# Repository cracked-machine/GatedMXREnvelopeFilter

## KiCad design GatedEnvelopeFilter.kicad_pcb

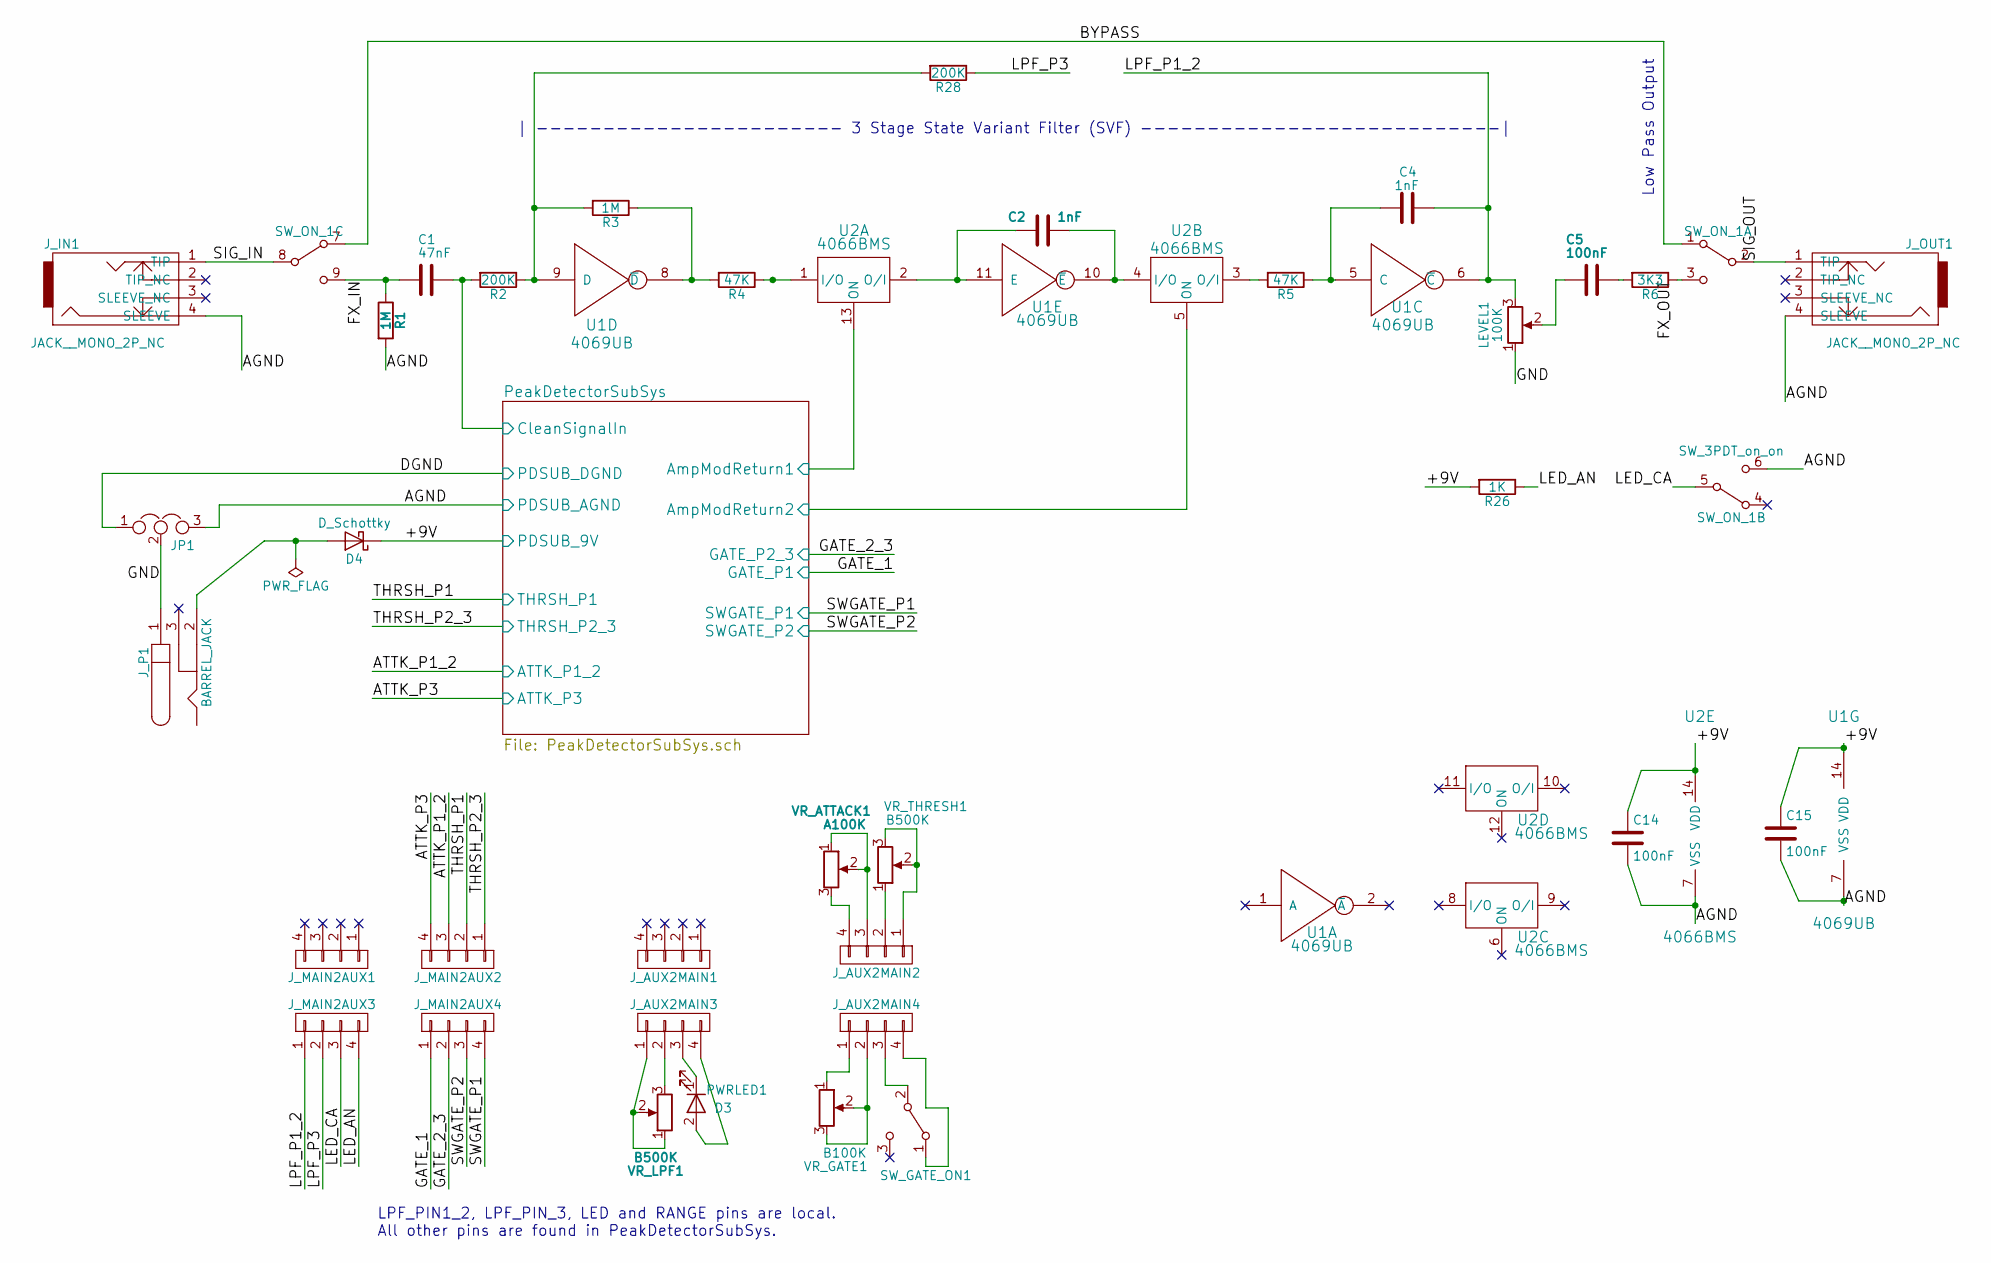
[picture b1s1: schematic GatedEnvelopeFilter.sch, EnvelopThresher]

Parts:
C1: 47nF; C_0805_HandSoldering
C2, C4: 1nF; C_0805_HandSoldering
C5, C14, C15: 100nF; C_0805_HandSoldering
D3: PWRLED1; LED_D5.0mm
D4: D_Schottky; D_SOD-123
JP1: Jumper_NC_Dual; NetTie-II_SMD
J_AUX2MAIN1, J_AUX2MAIN2, J_AUX2MAIN3, J_AUX2MAIN4: CONN_01X04; Pin_Header_Straight_1x04_Pitch2.54mm
J_IN1: JACK__MONO_2P_NC; NeutrikAudioSocket_Mono_PCB_NARROWPADS
J_MAIN2AUX1, J_MAIN2AUX2, J_MAIN2AUX3, J_MAIN2AUX4: CONN_01X04; Pin_Header_Straight_1x04_Pitch2.54mm
J_OUT1: JACK__MONO_2P_NC; NeutrikAudioSocket_Mono_PCB_NARROWPADS
J_P1: BARREL_JACK
LEVEL1: 100K
R1, R3: 1M; R_0805_HandSoldering
R2, R28: 200K; R_0805_HandSoldering
R4, R5: 47K; R_0805_HandSoldering
R6: 3K3; R_0805_HandSoldering
R26: 1K; R_0805_HandSoldering
SW_GATE_ON1: SW_SPDT; SW_SPDT_W6.86MM_L12.7MM_P4.8MM_D2MM
SW_ON_1: SW_3PDT_on_on; SW_3PDT_W18MM_L17.3MM_P5.3MM_D2MM_SolderLugs
U1: 4069UB; SOIC-14_3.9x8.7mm_Pitch1.27mm
U2: 4066BMS; SOIC-14_3.9x8.7mm_Pitch1.27mm
VR_ATTACK1: A100K; Potentiometer_Bourns_PTV09A-1_Horizontal
VR_GATE1: B100K; Potentiometer_Bourns_PTV09A-1_Horizontal
VR_LPF1: B500K; Potentiometer_Bourns_PTV09A-1_Horizontal
VR_THRESH1: B500K; Potentiometer_Bourns_PTV09A-1_Horizontal

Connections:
/+9V: C14.1, C15.1, D4.1 (K), R26.2, U1.14 (VDD), U2.14 (VDD); also elsewhere on the board
/AGND: C14.2, C15.2, JP1.3, J_IN1.4 (SLEEVE), J_OUT1.4 (SLEEVE), R1.2, SW_ON_1.6 (C), U1.7 (VSS), U2.7 (VSS); also elsewhere on the board
/ATTK_P1_2: J_MAIN2AUX2.3; also elsewhere on the board
/ATTK_P3: J_MAIN2AUX2.4; also elsewhere on the board
/BYPASS: SW_ON_1.1 (A), SW_ON_1.7 (A)
/DGND: JP1.1; also elsewhere on the board
/FX_IN: C1.2, R1.1, SW_ON_1.9 (C)
/FX_OUT: R6.1, SW_ON_1.3 (C)
/GATE_1: J_MAIN2AUX4.1; also elsewhere on the board
/GATE_2_3: J_MAIN2AUX4.2; also elsewhere on the board
/GND: JP1.2, J_P1.1, LEVEL1.1
/LED_AN: J_MAIN2AUX3.4, R26.1
/LED_CA: J_MAIN2AUX3.3, SW_ON_1.5 (B)
/LPF_P1_2: C4.1, C5.2, J_MAIN2AUX3.1, LEVEL1.2, LEVEL1.3, U1.6 (~C)
/LPF_P3: J_MAIN2AUX3.2, R28.1
/PeakDetectorSubSys/AmpModReturn1: U2.5 (ON), U2.13 (ON); also elsewhere on the board
/PeakDetectorSubSys/CleanSignalIn: C1.1, R2.2; also elsewhere on the board
/SIG_IN: J_IN1.1 (TIP), SW_ON_1.8 (B)
/SIG_OUT: J_OUT1.1 (TIP), SW_ON_1.2 (B)
/SWGATE_P1: J_MAIN2AUX4.4; also elsewhere on the board
/SWGATE_P2: J_MAIN2AUX4.3; also elsewhere on the board
/THRSH_P1: J_MAIN2AUX2.2; also elsewhere on the board
/THRSH_P2_3: J_MAIN2AUX2.1; also elsewhere on the board
unnamed: C2.1, U1.10 (~E), U2.4 (I/O)
unnamed: C2.2, U1.11 (E), U2.2 (O/I)
unnamed: C4.2, R5.1, U1.5 (C)
unnamed: C5.1, R6.2
unnamed: D3.1 (K), J_AUX2MAIN3.3
unnamed: D3.2 (A), J_AUX2MAIN3.4
unnamed: D4.2 (A), J_P1.2
unnamed: J_AUX2MAIN2.1, VR_THRESH1.2, VR_THRESH1.3
unnamed: J_AUX2MAIN2.2, VR_THRESH1.1
unnamed: J_AUX2MAIN2.3, VR_ATTACK1.1, VR_ATTACK1.2
unnamed: J_AUX2MAIN2.4, VR_ATTACK1.3
unnamed: J_AUX2MAIN3.1, VR_LPF1.1, VR_LPF1.2
unnamed: J_AUX2MAIN3.2, VR_LPF1.3
unnamed: J_AUX2MAIN4.1, VR_GATE1.1
unnamed: J_AUX2MAIN4.2, VR_GATE1.2, VR_GATE1.3
unnamed: J_AUX2MAIN4.3, SW_GATE_ON1.2 (B)
unnamed: J_AUX2MAIN4.4, SW_GATE_ON1.1 (A)
unnamed: R2.1, R3.2, R28.2, U1.9 (D)
unnamed: R3.1, R4.2, U1.8 (~D)
unnamed: R4.1, U2.1 (I/O)
unnamed: R5.2, U2.3 (O/I)

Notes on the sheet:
| ----------------------- 3 Stage State Variant Filter (SVF) ---------------------------|
Low Pass Output
LPF_PIN1_2, LPF_PIN_3, LED and RANGE pins are local. All other pins are found in PeakDetectorSubSys.

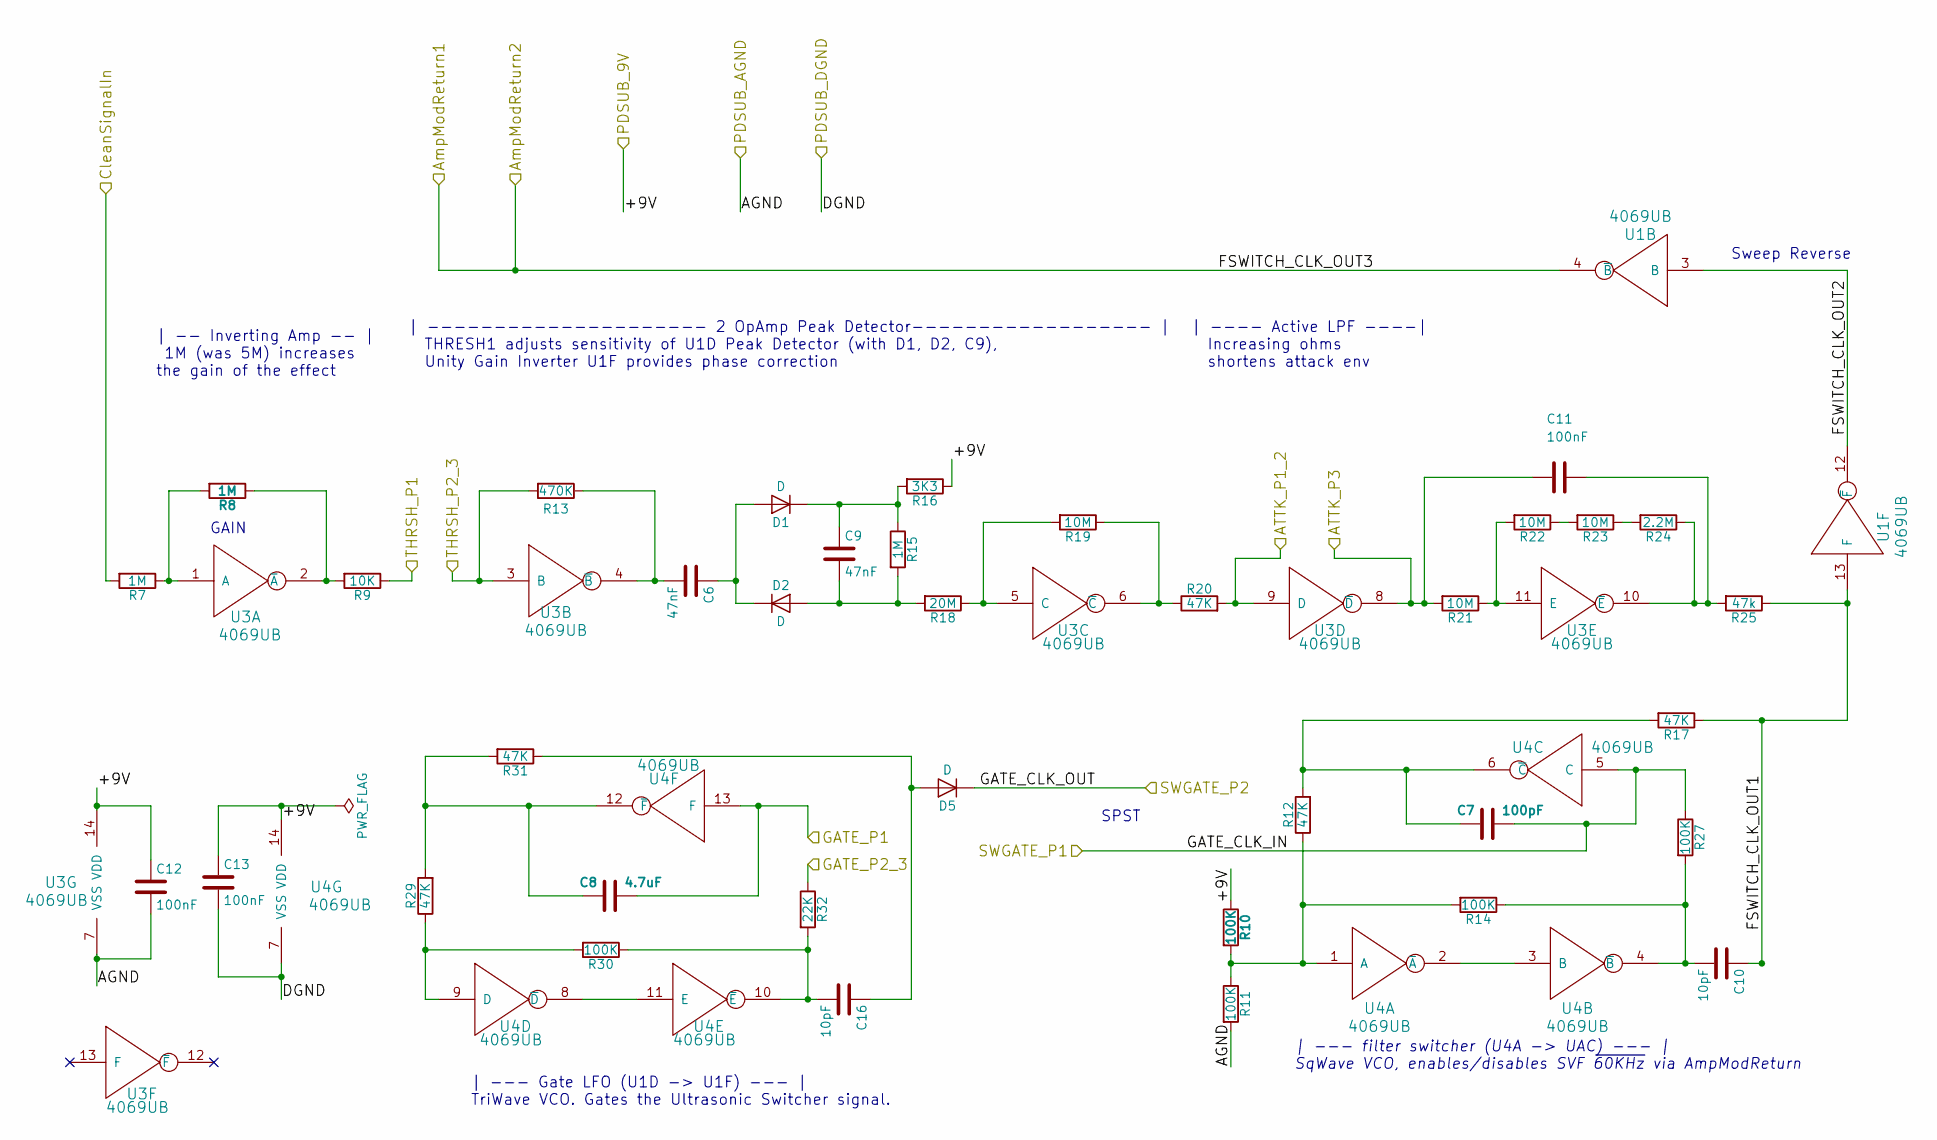
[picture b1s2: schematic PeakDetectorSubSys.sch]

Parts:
C6, C9: 47nF; C_0805_HandSoldering
C7: 100pF; C_0805_HandSoldering
C8: 4.7uF; C_0805_HandSoldering
C10, C16: 10pF; C_0805_HandSoldering
C11, C12, C13: 100nF; C_0805_HandSoldering
D1, D2, D5: D; D_SOD-123
R7, R8, R15: 1M; R_0805_HandSoldering
R9: 10K; R_0805_HandSoldering
R10, R11, R14, R27, R30: 100K; R_0805_HandSoldering
R12, R17, R20, R29, R31: 47K; R_0805_HandSoldering
R13: 470K; R_0805_HandSoldering
R16: 3K3; R_0805_HandSoldering
R18: 20M; R_0805_HandSoldering
R19, R21, R22, R23: 10M; R_0805_HandSoldering
R24: 2.2M; R_0805_HandSoldering
R25: 47k; R_0805_HandSoldering
R32: 22K; R_0805_HandSoldering
U1, U3, U4: 4069UB; SOIC-14_3.9x8.7mm_Pitch1.27mm

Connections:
/+9V: C12.1, C13.1, R10.1, R16.1, U3.14 (VDD), U4.14 (VDD); also elsewhere on the board
/AGND: C12.2, R11.2, U3.7 (VSS); also elsewhere on the board
/ATTK_P1_2: R20.2, U3.9 (D); also elsewhere on the board
/ATTK_P3: C11.2, R21.2, U3.8 (~D); also elsewhere on the board
/DGND: C13.2, U4.7 (VSS); also elsewhere on the board
/GATE_1: C8.1, U4.13 (F); also elsewhere on the board
/GATE_2_3: R32.1; also elsewhere on the board
/PeakDetectorSubSys/AmpModReturn1: U1.4 (~B); also elsewhere on the board
/PeakDetectorSubSys/CleanSignalIn: R7.2; also elsewhere on the board
/PeakDetectorSubSys/FSWITCH_CLK_OUT1: C10.1, R17.1, R25.1, U1.13 (F)
/PeakDetectorSubSys/FSWITCH_CLK_OUT2: U1.3 (B), U1.12 (~F)
/SWGATE_P1: C7.1, R27.1, U4.5 (C); also elsewhere on the board
/SWGATE_P2: D5.1 (K); also elsewhere on the board
/THRSH_P1: R9.1; also elsewhere on the board
/THRSH_P2_3: R13.2, U3.3 (B); also elsewhere on the board
unnamed: C6.1, D1.2 (A), D2.1 (K)
unnamed: C6.2, R13.1, U3.4 (~B)
unnamed: C7.2, R12.2, R17.2, U4.6 (~C)
unnamed: C8.2, R29.2, R31.2, U4.12 (~F)
unnamed: C9.1, D1.1 (K), R15.1, R16.2
unnamed: C9.2, D2.2 (A), R15.2, R18.2
unnamed: C10.2, R14.1, R27.2, U4.4 (~B)
unnamed: C11.1, R24.1, R25.2, U3.10 (~E)
unnamed: C16.1, D5.2 (A), R31.1
unnamed: C16.2, R30.1, R32.2, U4.10 (~E)
unnamed: R7.1, R8.2, U3.1 (A)
unnamed: R8.1, R9.2, U3.2 (~A)
unnamed: R10.2, R11.1, R12.1, R14.2, U4.1 (A)
unnamed: R18.1, R19.2, U3.5 (C)
unnamed: R19.1, R20.1, U3.6 (~C)
unnamed: R21.1, R22.2, U3.11 (E)
unnamed: R22.1, R23.2
unnamed: R23.1, R24.2
unnamed: R29.1, R30.2, U4.9 (D)
unnamed: U4.2 (~A), U4.3 (B)
unnamed: U4.8 (~D), U4.11 (E)

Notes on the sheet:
| ---- Active LPF ----| Increasing ohms shortens attack env
Sweep Reverse
| --------------------- 2 OpAmp Peak Detector------------------ | THRESH1 adjusts sensitivity of U1D Peak Detector (with D1, D2, C9), Unity Gain Inverter U1F provides phase correction
| --- filter switcher (U4A -> UAC) --- | SqWave VCO, enables/disables SVF ~60KHz via AmpModReturn
| -- Inverting Amp -- | 1M (was 5M) increases the gain of the effect
GAIN
| --- Gate LFO (U1D -> U1F) --- | TriWave VCO. Gates the Ultrasonic Switcher signal.
SPST

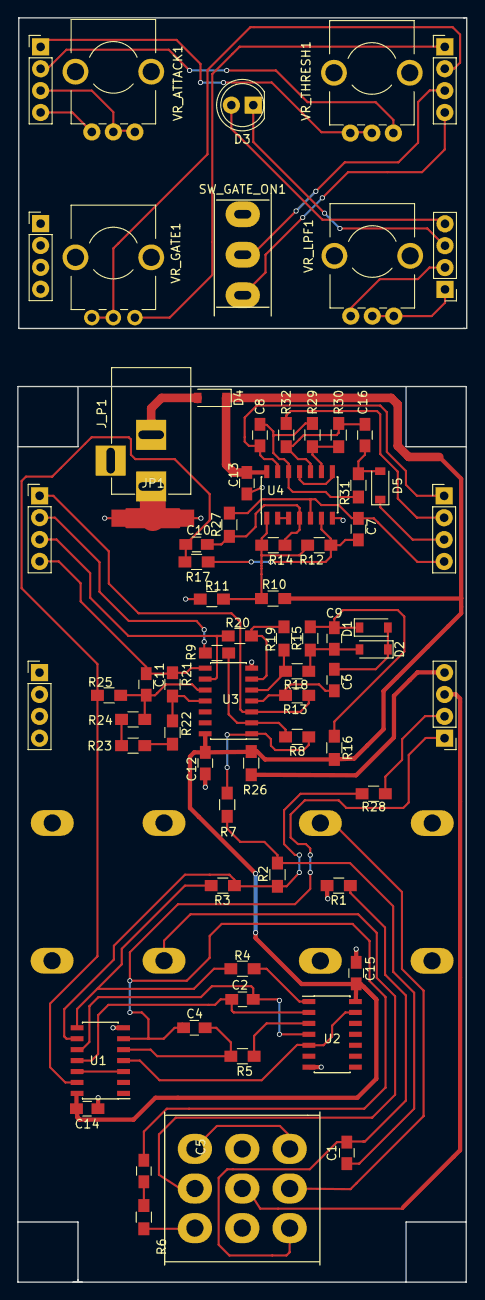
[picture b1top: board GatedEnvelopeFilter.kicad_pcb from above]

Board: 2 copper layers, 52.1 x 146.8 mm, 74 parts (0 on the bottom side), 67 nets.

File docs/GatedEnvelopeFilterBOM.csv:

Reference, Value, Footprint, Datasheet
"C1","47nF","Capacitors_SMD:C_0805_HandSoldering",""
"R2","200K","Resistors_SMD:R_0805_HandSoldering",""
"R3","1M","Resistors_SMD:R_0805_HandSoldering",""
"R4","47K","Resistors_SMD:R_0805_HandSoldering",""
"R5","47K","Resistors_SMD:R_0805_HandSoldering",""
"C4","1nF","Capacitors_SMD:C_0805_HandSoldering",""
"C5","100nF","Capacitors_SMD:C_0805_HandSoldering",""
"R6","3K3","Resistors_SMD:R_0805_HandSoldering",""
"J_IN1","JACK__MONO_2P_NC","NeutrikAudioJack:NeutrikAudioSocket_Mono_PCB_NARROWPADS",""
"J_OUT1","JACK__MONO_2P_NC","NeutrikAudioJack:NeutrikAudioSocket_Mono_PCB_NARROWPADS",""
"D4","D_Schottky","Diodes_SMD:D_SOD-123",""
"J_P1","BARREL_JACK","Connectors:BARREL_JACK",""
"SW_ON_1","SW_3PDT_on_on","custom_sw:SW_3PDT_W18MM_L17.3MM_P5.3MM_D2MM_SolderLugs",""
"D3","PWRLED1","LEDs:LED_D5.0mm",""
"R26","1K","Resistors_SMD:R_0805_HandSoldering",""
"U1","4069UB","Housings_SOIC:SOIC-14_3.9x8.7mm_Pitch1.27mm",""
"R1","1M","Resistors_SMD:R_0805_HandSoldering",""
"C2","1nF","Capacitors_SMD:C_0805_HandSoldering",""
"U2","4066BMS","Housings_SOIC:SOIC-14_3.9x8.7mm_Pitch1.27mm",""
"VR_LPF1","B500K","Potentiometers:Potentiometer_Bourns_PTV09A-1_Horizontal",""
"VR_THRESH1","B500K","Potentiometers:Potentiometer_Bourns_PTV09A-1_Horizontal",""
"VR_ATTACK1","A100K","Potentiometers:Potentiometer_Bourns_PTV09A-1_Horizontal",""
"J_MAIN2AUX1","CONN_01X04","Pin_Headers:Pin_Header_Straight_1x04_Pitch2.54mm",""
"J_MAIN2AUX2","CONN_01X04","Pin_Headers:Pin_Header_Straight_1x04_Pitch2.54mm",""
"J_MAIN2AUX3","CONN_01X04","Pin_Headers:Pin_Header_Straight_1x04_Pitch2.54mm",""
"J_MAIN2AUX4","CONN_01X04","Pin_Headers:Pin_Header_Straight_1x04_Pitch2.54mm",""
"J_AUX2MAIN1","CONN_01X04","Pin_Headers:Pin_Header_Straight_1x04_Pitch2.54mm",""
"J_AUX2MAIN2","CONN_01X04","Pin_Headers:Pin_Header_Straight_1x04_Pitch2.54mm",""
"J_AUX2MAIN3","CONN_01X04","Pin_Headers:Pin_Header_Straight_1x04_Pitch2.54mm",""
"J_AUX2MAIN4","CONN_01X04","Pin_Headers:Pin_Header_Straight_1x04_Pitch2.54mm",""
"C14","100nF","Capacitors_SMD:C_0805_HandSoldering",""
"C15","100nF","Capacitors_SMD:C_0805_HandSoldering",""
"R28","200K","Resistors_SMD:R_0805_HandSoldering",""
"VR_GATE1","B100K","Potentiometers:Potentiometer_Bourns_PTV09A-1_Horizontal",""
"SW_GATE_ON1","SW_SPDT","custom_sw:SW_SPDT_W6.86MM_L12.7MM_P4.8MM_D2MM",""
"JP1","Jumper_NC_Dual","Oddities:NetTie-II_SMD",""
"R7","1M","Resistors_SMD:R_0805_HandSoldering",""
"R9","10K","Resistors_SMD:R_0805_HandSoldering",""
"R8","1M","Resistors_SMD:R_0805_HandSoldering",""
"R13","470K","Resistors_SMD:R_0805_HandSoldering",""
"C6","47nF","Capacitors_SMD:C_0805_HandSoldering",""
"D1","D","Diodes_SMD:D_SOD-123",""
"D2","D","Diodes_SMD:D_SOD-123",""
"C9","47nF","Capacitors_SMD:C_0805_HandSoldering",""
"R15","1M","Resistors_SMD:R_0805_HandSoldering",""
"R18","20M","Resistors_SMD:R_0805_HandSoldering",""
"R19","10M","Resistors_SMD:R_0805_HandSoldering",""
"R20","47K","Resistors_SMD:R_0805_HandSoldering",""
"R21","10M","Resistors_SMD:R_0805_HandSoldering",""
"R22","10M","Resistors_SMD:R_0805_HandSoldering",""
"C11","100nF","Capacitors_SMD:C_0805_HandSoldering",""
"R25","47k","Resistors_SMD:R_0805_HandSoldering",""
"R17","47K","Resistors_SMD:R_0805_HandSoldering",""
"C7","100pF","Capacitors_SMD:C_0805_HandSoldering",""
"R14","100K","Resistors_SMD:R_0805_HandSoldering",""
"R12","47K","Resistors_SMD:R_0805_HandSoldering",""
"C10","10pF","Capacitors_SMD:C_0805_HandSoldering",""
"R10","100K","Resistors_SMD:R_0805_HandSoldering",""
"R11","100K","Resistors_SMD:R_0805_HandSoldering",""
"U4","4069UB","Housings_SOIC:SOIC-14_3.9x8.7mm_Pitch1.27mm",""
"U3","4069UB","Housings_SOIC:SOIC-14_3.9x8.7mm_Pitch1.27mm",""
"R16","3K3","Resistors_SMD:R_0805_HandSoldering",""
"R23","10M","Resistors_SMD:R_0805_HandSoldering",""
"R24","2.2M","Resistors_SMD:R_0805_HandSoldering",""
"C12","100nF","Capacitors_SMD:C_0805_HandSoldering",""
"C13","100nF","Capacitors_SMD:C_0805_HandSoldering",""
"R27","100K","Resistors_SMD:R_0805_HandSoldering",""
"R31","47K","Resistors_SMD:R_0805_HandSoldering",""
"C8","4.7uF","Capacitors_SMD:C_0805_HandSoldering",""
"R30","100K","Resistors_SMD:R_0805_HandSoldering",""
"R29","47K","Resistors_SMD:R_0805_HandSoldering",""
"C16","10pF","Capacitors_SMD:C_0805_HandSoldering",""
"R32","22K","Resistors_SMD:R_0805_HandSoldering",""
"D5","D","Diodes_SMD:D_SOD-123",""

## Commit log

2018-03-17 First Upload
2018-03-17 Set theme jekyll-theme-midnight
2018-03-17 Rename index.html to readme.md
2018-03-25 Added output level pot control
